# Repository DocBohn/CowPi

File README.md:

# CowPi Library

[//]: # ([![Depends on CowPi_stdio]&#40;https://img.shields.io/badge/🐮_𝜋_depends_on-CowPi__stdio-crimson&#41;]&#40;https://github.com/DocBohn/CowPi_stdio&#41;)
[//]: # (scarlet)
[)](https://github.com/DocBohn/CowPi_stdio)

## What is the Cow Pi?

### The hardware

The Cow Pi is a simple circuit that consists of a microcontroller board, a
display module, a couple of LEDs, a couple of momentary buttons, a couple of
maintained switches, and a matrix keypad. We use it to teach memory-mapped I/O,
polling, and interrupts.

### The library

Initially we supported the memory-mapped I/O lab with a header file that
defined some `struct`s and named constants. Later we added some macros to reduce
complexity that didn't contribute to the learning objectives.

We decided to create a library for three reasons:
- It allows us to provide some additional bootstrapping for students: they'll
  be able to work on polling logic using some of the functions in the library
  and then later replace those with functions that use memory-mapped I/O. Or
  they can start with memory-mapped I/O and then move on to the polling logic.
  Before the library, students had no choice but to start with memory-mapped
  I/O.
- It allows us to replace parameterized macros with functions.
- We can use more complex display modules. Originally, the Cow Pi's display
  module was an 8-digit/7-segment display module. The Terasic Altera DE1 boards
  that we used to use had a 4-digit/7-segment display. Manipulating 7-segment
  displays is incredibly easy. To simplify the supply chain for our supplier,
  we're going to try using 2-row/16-column LCD display modules. Manipulating
  the LCD1602 display modules is not incredibly easy. With a library, we can let
  students focus on the memory-mapped I/O aspect and not on the details of
  controlling the display module.

## Why is it called the *Cow Pi*?

Because it's punny.

### No, I mean, *-Pi* is typically used as a suffix for circuits that use a Raspberry Pi instead of an Arduino.

Typically, yes, but *Cowduino* isn't very punny, is it?

Besides, there soon will be a version of the Cow Pi that makes use of the
Raspberry Pi Pico. That's why we said that the circuit has "a microcontroller
board" instead of "an Arduino Nano."

## Why did you design something new? Didn't you consider something manufactured?

We used to use the [Terasic Altera
DE1](https://www.terasic.com.tw/cgi-bin/page/archive.pl?No=83). Our computer
science students and software engineering students didn't reprogram the FPGA;
they simply used C and compiled their programs to run on the Nios II soft core
that came pre-programmed into the FPGA. When we decided it was time to stop
using the DE1s, our computer engineering students switched to the [Terasic
DE10-Lite](http://de10-lite.terasic.com/), but we decided that the cost was too
great for the features that our CS and SE students would use.

The problem we ran into with the various Arduino shields or Raspberry Pi hats is
that they either were unavailable in the quantity we needed, or would require
our students to solder them together -- and we have no expectations that our
CS and SE students are able to solder. We were pretty sure that they could put
together a circuit on a solderless breadboard, though.

We are, however, planning to have PCBs manufactured and assembled, assuming we
can keep the cost down.

## The Cow Pi uses nearly all of the pins on the Arduino Nano; that'll make it hard to do any other projects with it.

Yes, that's true. The Cow Pi is designed to support specific learning
objectives. If you want to do a different project, then disassemble the kit and
use the parts to build your project.

## Why don't you just use existing libraries like `LiquidCrystal` and `Wire`?

Because those libraries hide the details. Part of what we use the Cow Pi for is
teaching memory-mapped I/O.

## Have you considered making the CowPi library work with MicroPython or CircuitPython?

😐

Python isn't exactly known for being a language that exposes the underlying
hardware. While it's possible to make the library work with MicroPython and/or
CircuitPython, that'd defeat the point of the library being a way to hide
*only* the complexities that are unrelated to memory-mapped I/O,
polling, and interrupts.

## Are you going to make it work with the XYZ microcontroller board?

Probably.

The Cow Pi works with the Arduino Nano and the Arduino Uno.

We have plans to make it work with the Arduino Mega 2560, the Arduino Nano
Every, the Arduino Nano 33 IOT, and the Raspberry Pi Pico (both using the
Arduino framework and using the Pico SDK). Probably the Raspberry Pi 4 and 400,
too. Eventually the Arduino Nano 33 BLE Sense, the Arduino RP2040 Connect, and
the Arduino Uno WiFi & Arduino Uno R4 (but we don't have samples of any of these laying
around).

### What about the STM32 "Blue Pill," or something in the Adafruit Feather family, or the SparkFun Teensy family, or...?

If there's interest using one of these microcontroller boards for the Cow Pi,
we can certainly look into it.

Similarly, if there's interest in a different display module, we can look into
it.

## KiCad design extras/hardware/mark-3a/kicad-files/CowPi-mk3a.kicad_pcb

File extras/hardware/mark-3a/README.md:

# Cow Pi Mark 3a PCB Assembly Notes

- I2C or SPI
  - There is a pair of solder jumpers on the left side of the board. Creating a
    solder bridge from each center pad to its top pad will connect the
    slide-switches to Arduino pins `D10` and `D11`, freeing the pins used for
    I2C. Creating a bridge from each center pad to its bottom pad will connect
    the slide-switches to pins `D18/A4` and `D19/A5`, freeing the pins used
    for SPI.
  - For I2C, the display module will be driven by a [common I2C interface board
    for LCD character displays](https://www.google.com/search?q=i2c+adapter+for+lcd+1602).
    Before soldering the interface module to the PCB, solder short wires to the
    `GND`, `5V`, `SDA`, and `SCL` solder pads near the located between the
    Arduino's footprint and the mini-breadboard's footprint. After soldering the
    interface module to the PCB, solder the other ends of those wires to the
    interface module's I2C headers.
  - For SPI, you'll need a 10kΩ trim potentiometer (the files in the repo are
    set up for 3 inline pins since that's what's in my junk drawer; you'll
    need to change the footprint if you want a different pin arrangement), a
    10kΩ fixed resistor, an NPN transistor (I'm using 2N2222), and a 74HC595
    shift register. If you want to have the option to disable the display
    module, then you'll also need a 3-pin male header and a shunt jumper;
    otherwise, you can create a solder bridge from the center `SPI-LCD1602
    Disable/Enable` hole to the `Enable` hole.
- Common [2-row, 16-column LCD character display](https://www.google.com/search?q=lcd+1602+display+module)
  ("LCD1602") driven by Hitachi HD44780 LCD controller.
- Slide-switches: two (2) common 3-pin, 2.54mm (0.1in) pitch, breadboard-mountable
  switches
- Tactile switches (buttons): nineteen (19) 6mm, 4-prong tactile switches
  (you could use only 18 if you omit the `RESET` button and just use the one
  on the Arduino)
- Diodes: sixteen (16) diodes; I originally planned to use 1N4001 but got a good
  deal on 1N4448. These are to permit safe and accurate reading of multiple
  keypad buttons simultaneously (not yet supported in the library a/o v0.3.0).
  If you'll only ever press one keypad button at a time, then you can create
  solder bridges across the diode holes instead of inserting diodes.
- LEDs: two (2) common LEDs. I like to use red for left and green for right, to
  match navigation lights, but that's not necessary. You can omit the left LED
  since it duplicate's the Arduino's build-in LED. For that matter, the left
  LED is nigh-useless when using SPI.
- Current-limiting resistors: two (2) common resistors. I spec'd 470Ω, but
  the value isn't critical as long as your choice sufficiently limits the current
  into the LEDs and leaves the LED bright enough to see.
- External power jack (optional): 2.1mm barrel connector
- 4-input NAND -- because of the limited number of external interrupts on the
  ATmega328P (and, by exension, the Arduino Nano), we use NANDs to generate
  the interrupt signals for the keypad and for the left/right buttons. (Early
  testing confirms that the NANDs won't be needed when using an Arduino Nano
  Every due to the ample external interrupts, but the CowPi library doesn't yet
  support that (a/o v0.3.0).) We originally used 74LS20, but *any* 74x20 should
  do (we're currently using 74HC20 because they're a little cheaper and also
  have a broader Vcc range). If you want to selectively break the connection
  from the 74x20 to the Arduino, then add two (2) 2-pin male headers to the
  appropriate location near the Arduino and close the circuit with shunt jumpers;
  if you think you'll never break that circuit, then you can create solder
  bridges where the male headers would otherwise go.
- Breakout header (optional): 2x8-pin, 2.54 (0.1in) pitch, female header. It
  doesn't break out all of the Arduino pins, only those that might be available
  for use by external components
- Mini-breadboard (optional): a convenient place to mount external components,
  also a convenient way to hide the order number printed on the PCB. Note that
  the mini-breadboard I used to measure the space needed didn't have interlocking
  tabs, and the mini-breadboards I ordered to place on the PCBs do -- those tabs
  make for a tight squeeze, so place the mini-breadboard on last.

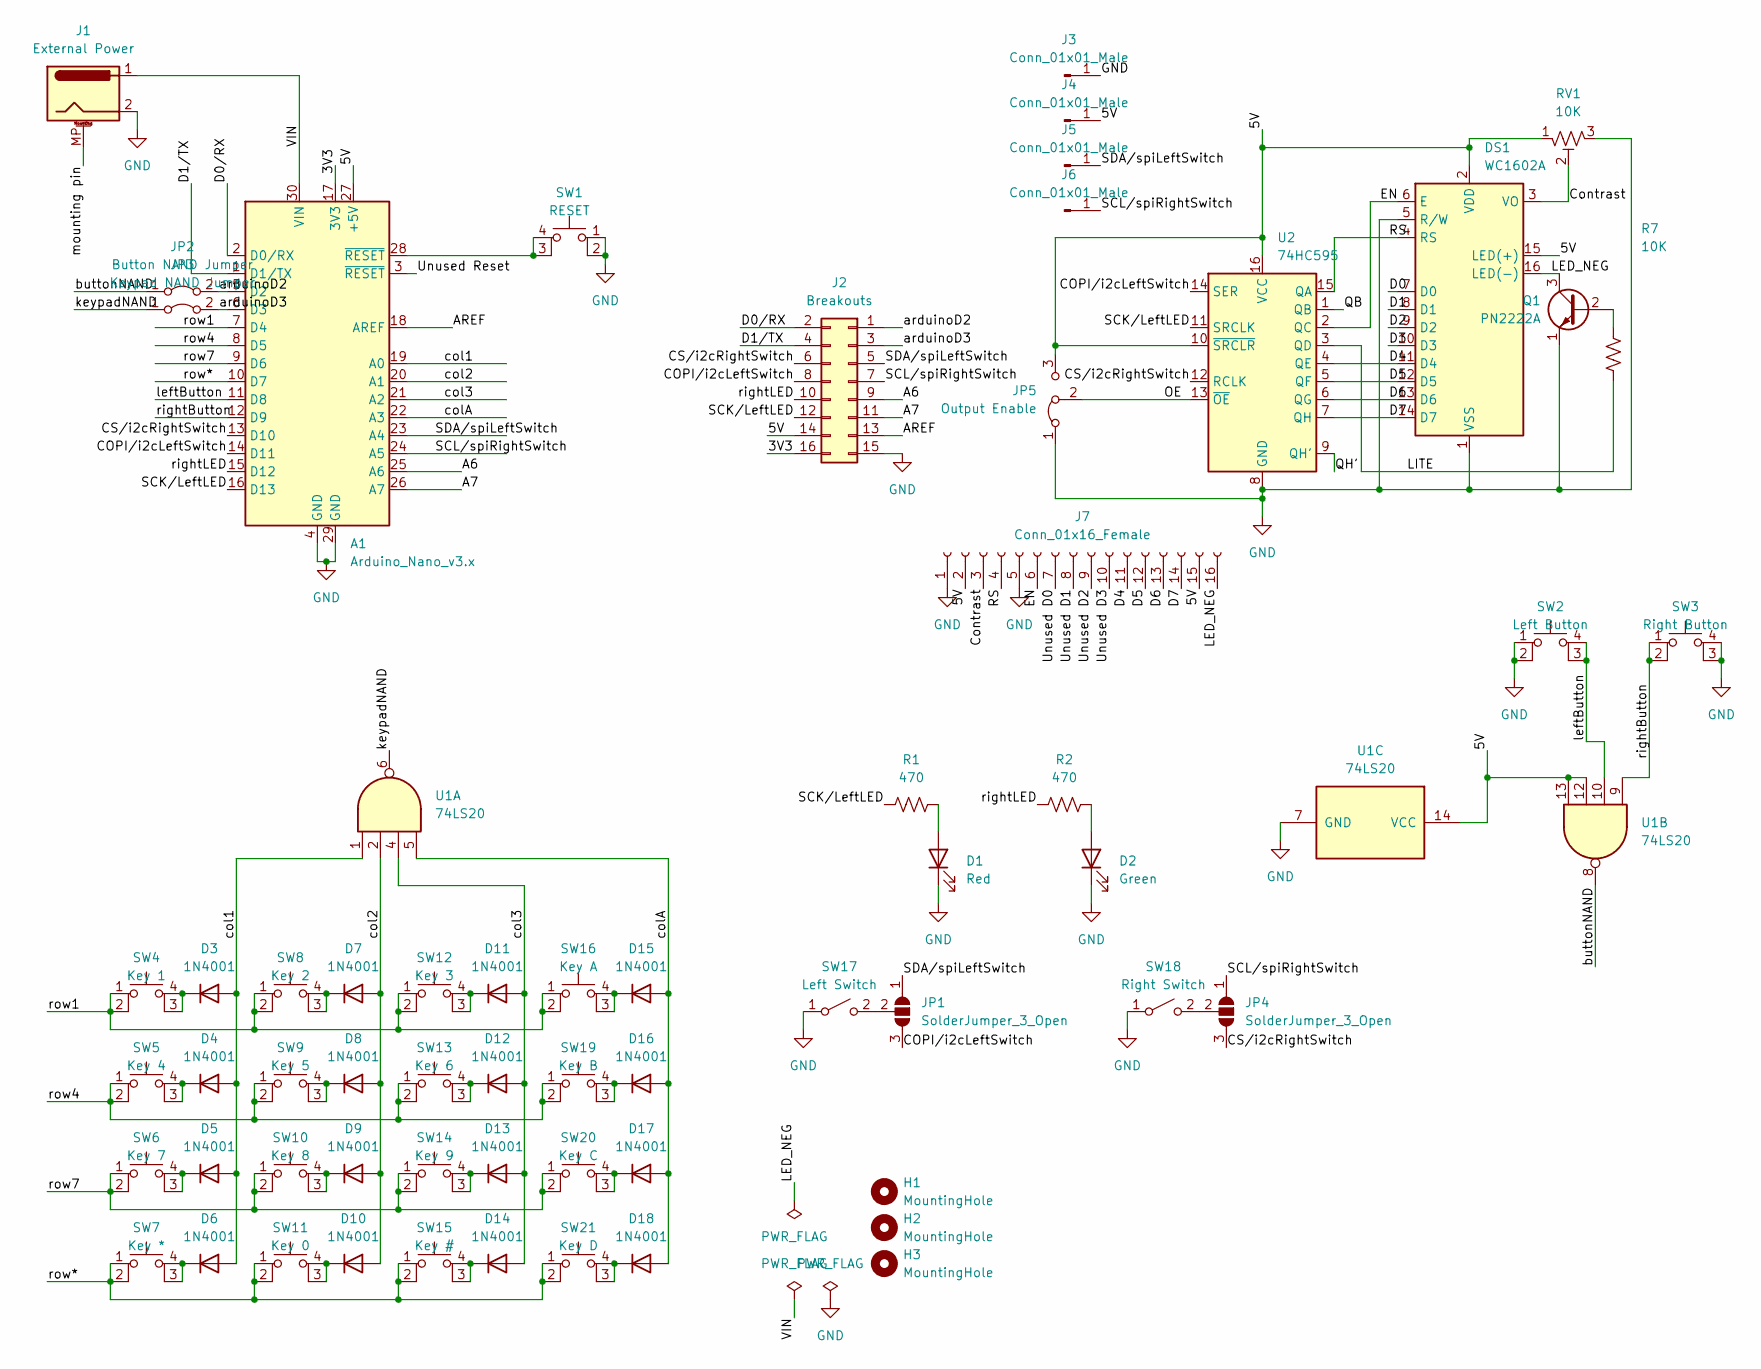
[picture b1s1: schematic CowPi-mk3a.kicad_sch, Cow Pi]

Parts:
A1: Arduino_Nano_v3.x; Arduino_Nano
D1: Red; LED_D5.0mm
D2: Green; LED_D5.0mm
D3, D4, D5, D6, D7, D8, D9, D10, D11, D12, D13, D14, D15, D16, D17, D18: 1N4001; D_DO-41_SOD81_P10.16mm_Horizontal
DS1: WC1602A
H1, H2, H3: MountingHole; MountingHole_3mm_Pad
J1: External Power; BarrelJack_Horizontal
J2: Breakouts; PinSocket_2x08_P2.54mm_Vertical
J3, J4, J5, J6: Conn_01x01_Male; TestPoint_Pad_D2.0mm
J7: Conn_01x16_Female; PinSocket_1x16_P2.54mm_Vertical
JP1, JP4: SolderJumper_3_Open; SolderJumper-3_P1.3mm_Open_RoundedPad1.0x1.5mm
JP2: Button NAND Jumper; PinHeader_1x02_P2.54mm_Vertical
JP3: Keypad NAND Jumper; PinHeader_1x02_P2.54mm_Vertical
JP5: Output Enable; PinHeader_1x03_P2.54mm_Vertical
Q1: PN2222A; TO-92_Inline
R1, R2: 470; R_Axial_DIN0309_L9.0mm_D3.2mm_P12.70mm_Horizontal
R7: 10K; R_Axial_DIN0309_L9.0mm_D3.2mm_P12.70mm_Horizontal
RV1: 10K; Potentiometer_Vishay_248GJ-249GJ_Single_Vertical
SW1: RESET; SW_PUSH_6mm_H5mm
SW2: Left Button; SW_PUSH_6mm_H5mm
SW3: Right Button; SW_PUSH_6mm_H5mm
SW4: Key 1; SW_PUSH_6mm_H5mm
SW5: Key 4; SW_PUSH_6mm_H5mm
SW6: Key 7; SW_PUSH_6mm_H5mm
SW7: Key *; SW_PUSH_6mm_H5mm
SW8: Key 2; SW_PUSH_6mm_H5mm
SW9: Key 5; SW_PUSH_6mm_H5mm
SW10: Key 8; SW_PUSH_6mm_H5mm
SW11: Key 0; SW_PUSH_6mm_H5mm
SW12: Key 3; SW_PUSH_6mm_H5mm
SW13: Key 6; SW_PUSH_6mm_H5mm
SW14: Key 9; SW_PUSH_6mm_H5mm
SW15: Key #; SW_PUSH_6mm_H5mm
SW16: Key A; SW_PUSH_6mm_H5mm
SW17: Left Switch; SW_Slide_1P2T_CK_OS102011MS2Q
SW18: Right Switch; SW_Slide_1P2T_CK_OS102011MS2Q
SW19: Key B; SW_PUSH_6mm_H5mm
SW20: Key C; SW_PUSH_6mm_H5mm
SW21: Key D; SW_PUSH_6mm_H5mm
U1: 74LS20; DIP-14_W7.62mm_Socket
U2: 74HC595; DIP-16_W7.62mm_Socket

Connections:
/3V3: A1.17 (3V3), J2.16
/5V: A1.27 (+5V), DS1.2 (VDD), DS1.15 (LED(+)), J2.14, J4.1, J7.2, J7.15, JP5.3 (B), RV1.1, U1.12, U1.13, U1.14 (VCC), U2.10 (~SRCLR), U2.16 (VCC)
/A6: A1.25 (A6), J2.9
/A7: A1.26 (A7), J2.11
/AREF: A1.18 (AREF), J2.13
/COPI/i2cLeftSwitch: A1.14 (D11), J2.8, JP1.3 (B), U2.14 (SER)
/CS/i2cRightSwitch: A1.13 (D10), J2.6, JP4.3 (B), U2.12 (RCLK)
/Contrast: DS1.3 (VO), J7.3, RV1.2
/D0: DS1.7 (D0)
/D0/RX: A1.2 (D0/RX), J2.2
/D1: DS1.8 (D1)
/D1/TX: A1.1 (D1/TX), J2.4
/D2: DS1.9 (D2)
/D3: DS1.10 (D3)
/D4: DS1.11 (D4), J7.11, U2.4 (QE)
/D5: DS1.12 (D5), J7.12, U2.5 (QF)
/D6: DS1.13 (D6), J7.13, U2.6 (QG)
/D7: DS1.14 (D7), J7.14, U2.7 (QH)
/EN: DS1.6 (E), J7.6, U2.2 (QC)
/LED_NEG: DS1.16 (LED(-)), J7.16, Q1.3 (C)
/LITE: R7.2, U2.3 (QD)
/OE: JP5.2 (C), U2.13 (~OE)
/QB: U2.1 (QB)
/QH': U2.9 (QH')
/RS: DS1.4 (RS), J7.4, U2.15 (QA)
/SCK/LeftLED: A1.16 (D13), J2.12, R1.1, U2.11 (SRCLK)
/SCL/spiRightSwitch: A1.24 (A5), J2.7, J6.1, JP4.1 (A)
/SDA/spiLeftSwitch: A1.23 (A4), J2.5, J5.1, JP1.1 (A)
/Unused D0: J7.7
/Unused D1: J7.8
/Unused D2: J7.9
/Unused D3: J7.10
/Unused Reset: A1.3 (~RESET)
/VIN: A1.30 (VIN), J1.1
/arduinoD2: A1.5 (D2), J2.1, JP2.2 (B)
/arduinoD3: A1.6 (D3), J2.3, JP3.2 (B)
/buttonNAND: JP2.1 (A), U1.8
/col1: A1.19 (A0), D3.2 (A), D4.2 (A), D5.2 (A), D6.2 (A), U1.1
/col2: A1.20 (A1), D7.2 (A), D8.2 (A), D9.2 (A), D10.2 (A), U1.2
/col3: A1.21 (A2), D11.2 (A), D12.2 (A), D13.2 (A), D14.2 (A), U1.4
/colA: A1.22 (A3), D15.2 (A), D16.2 (A), D17.2 (A), D18.2 (A), U1.5
/keypadNAND: JP3.1 (A), U1.6
/leftButton: A1.11 (D8), SW2.3 (K), SW2.4 (A), U1.10
/mounting pin: J1.MP (MountPin)
/rightButton: A1.12 (D9), SW3.1, SW3.2, U1.9
/rightLED: A1.15 (D12), J2.10, R2.1
/row1: A1.7 (D4), SW4.1, SW4.2, SW8.1, SW8.2, SW12.1, SW12.2, SW16.1, SW16.2
/row4: A1.8 (D5), SW5.1, SW5.2, SW9.1, SW9.2, SW13.1, SW13.2, SW19.1, SW19.2
/row7: A1.9 (D6), SW6.1, SW6.2, SW10.1, SW10.2, SW14.1, SW14.2, SW20.1, SW20.2
/row*: A1.10 (D7), SW7.1, SW7.2, SW11.1, SW11.2, SW15.1, SW15.2, SW21.1, SW21.2
GND: A1.4 (GND), A1.29 (GND), D1.1 (K), D2.1 (K), DS1.1 (VSS), DS1.5 (R/W), J1.2, J2.15, J3.1, J7.1, J7.5, JP5.1 (A), Q1.1 (E), RV1.3, SW1.1, SW1.2, SW2.1, SW2.2, SW3.3 (K), SW3.4 (A), SW17.1 (A), SW18.1 (A), U1.7 (GND), U2.8 (GND)
unnamed: A1.28 (~RESET), SW1.3 (K), SW1.4 (A)
unnamed: D1.2 (A), R1.2
unnamed: D2.2 (A), R2.2
unnamed: D3.1 (K), SW4.3 (K), SW4.4 (A)
unnamed: D4.1 (K), SW5.3 (K), SW5.4 (A)
unnamed: D5.1 (K), SW6.3 (K), SW6.4 (A)
unnamed: D6.1 (K), SW7.3 (K), SW7.4 (A)
unnamed: D7.1 (K), SW8.3 (K), SW8.4 (A)
unnamed: D8.1 (K), SW9.3 (K), SW9.4 (A)
unnamed: D9.1 (K), SW10.3 (K), SW10.4 (A)
unnamed: D10.1 (K), SW11.3 (K), SW11.4 (A)
unnamed: D11.1 (K), SW12.3 (K), SW12.4 (A)
unnamed: D12.1 (K), SW13.3 (K), SW13.4 (A)
unnamed: D13.1 (K), SW14.3 (K), SW14.4 (A)
unnamed: D14.1 (K), SW15.3 (K), SW15.4 (A)
unnamed: D15.1 (K), SW16.3 (K), SW16.4 (A)
unnamed: D16.1 (K), SW19.3 (K), SW19.4 (A)
unnamed: D17.1 (K), SW20.3 (K), SW20.4 (A)
unnamed: D18.1 (K), SW21.3 (K), SW21.4 (A)
unnamed: JP1.2 (C), SW17.2 (B)
unnamed: JP4.2 (C), SW18.2 (B)
unnamed: Q1.2 (B), R7.1

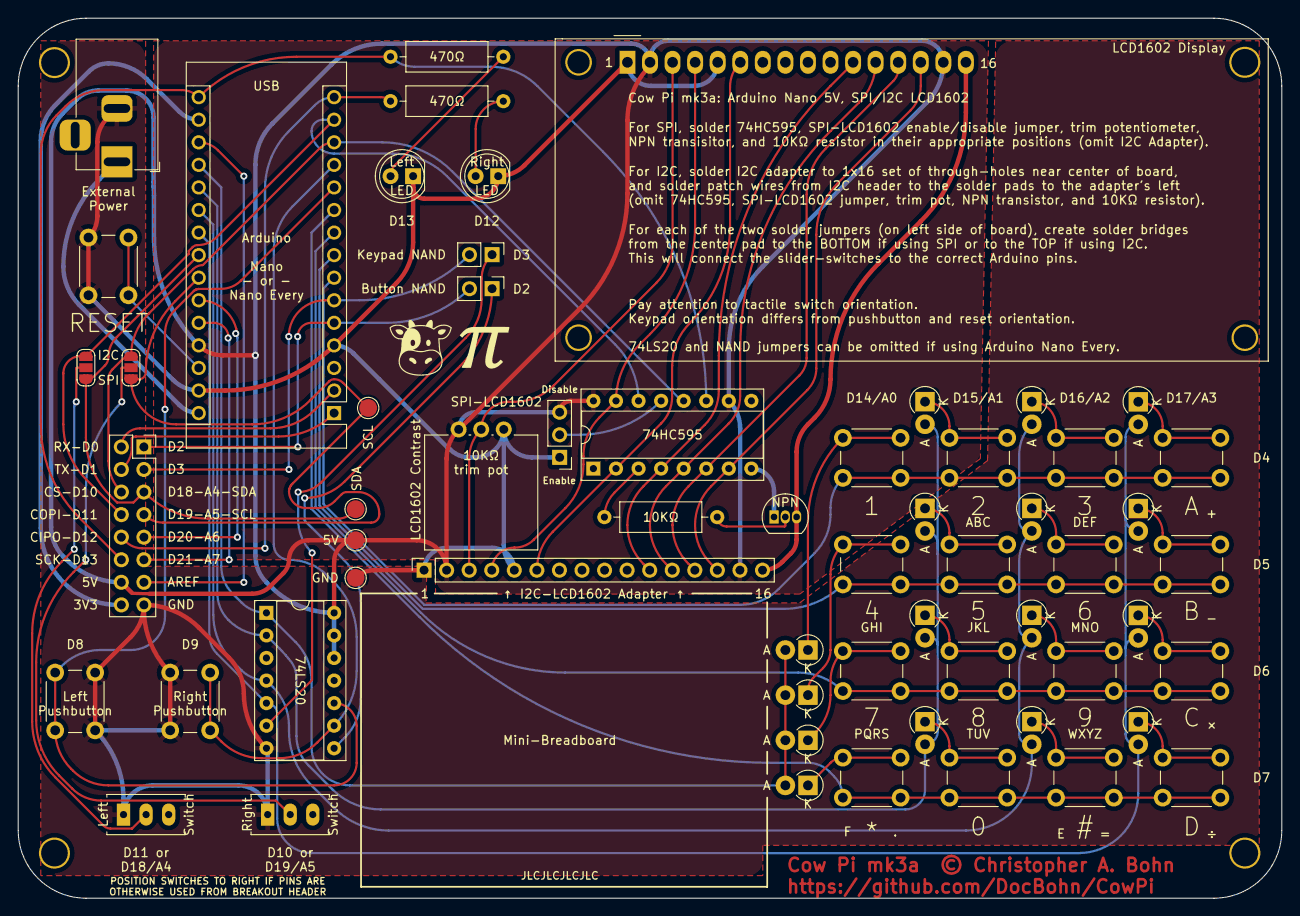
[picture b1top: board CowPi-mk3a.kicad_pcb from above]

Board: 2 copper layers, 142.2 x 99.1 mm, 63 parts (0 on the bottom side), 61 nets.

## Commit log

2022-08-17 Migrated CowPi library to its own repository
2022-08-18 Added Cow Pi hardware Mark 1 instructions and Mark 3a PCB files
2022-10-06 Making progress on datasheet
2022-11-08 datasheet ready for PollingLab
2022-11-16 added ATmega328P-specific data to datasheet
2022-11-16 removed doxygen files from datasheet directory
2023-01-26 Resolved problem with symbols being introduced too often. Fixes #3
    - Migrated font constants to "internal" headers that are imported *only*
    by cowpi_fonts.c.
    - Replaced `cowpi_io_base` constant pointer with `COWPI_IO_BASE` macro
2023-01-26 Removed error detection from default I2C code. Fixes #2
    Besides requiring the "one additional handshake" the error detection
    code suggested in the ATmega328P datasheet was also causing problems
    when included in student code. Experimentation in a simulator indicated
    that a "data received ACK" was present after a START bit was sent. My
    working hypothesis is that the problem happens when the system is reset
    while the I2C peripheral is expecting data, causing a misinterpretation
2023-01-26 Created COWPI_DEFAULT mapping for SPI control of LCD1602. Closes #1
2023-01-26 Added the verb "is" to functions that detect switches' position.
2023-01-26 Documentation updates for change to version 0.4
2023-03-19 Changes in preparation for Spring 2023 PollingLab
    The biggest change is a new table that shows which devices are read
    from or written to by which bits in the I/O registers.
2023-04-05 updated diagrams
2023-04-06 Removed bug that constrained the include order for nested headers
    When the Arduino IDE autommatically included a nested header file
    upon auto-complete, it caused some headers (such as cowpi_io.h)
    that depended on stdbool.h to be included before stdbool.h was
    included.
    The fix is to make sure that the nested headers include any
    standard headers they actually depend on, instead of relying on
2023-04-29 Inserted use of "dummy_pgmspace" into appropriate files
2023-05-09 Added file streams for top and bottom rows of LCD1602 display
    Allows use of `fprintf` to send strings to the display module
2023-05-16 Added file stream for full LCD1602 display
    Where the row-based file streams allow the programmer to determine text
    placement by using one stream or another, the full-display file stream
    requires the programmer to use ASCII placement codes -- but it's
    possible that the `\n` behavior is more intuitive by doing so.
    It's probable that only one approach or the other will still be around
    when we get to the 1.0 release.
2023-05-17 Added functions to register/deregister ISR for changes on any Nano pin
    Strictly speaking, there are still just the three ISRs, one for each
    "real" pin change interrupt. The actual ISRs then check which pin had
    the change and call the appropriate interrupt handler that the
    programmer registered.
2023-05-20 Replaced Wokwi diagram files (closes #12)
    While Wokwi now has logic gates, the ability to register ISRs for
    changes on specific pins other than D2 & D3 (see commit b362454), logic
    gates are no longer necessary.
    We now have a template diagram, as well as diagrams with specific
    display modules.
2023-07-06 Updated library manifests
2023-07-06 Removed Display-Related Code
    All code related to display modules and to stdin/stdout is now in the
    CowPi_stdio library.
2023-07-07 Default kepad implementation can handle different microcontroller boards
2023-07-07 Added function to read chorded keypresses
    This function should only be called when diodes protect the keys!
2023-07-24 Updated `cowpi_setup` to use `CowPi_stdio` configuration structures
    Also some internal file re-arranging.
2023-07-31 Removed Doxygen groups to better support Breathe and ReadTheDocs
2023-08-02 Push to v0.6
2023-08-13 Added pin mappings for Raspberry Pi Pico
    Still no memory mapped I/O structures.
    Still only for Arduino framework.
2023-10-14 Added Nyquist Rate check to debouncing code
2023-11-25 Added structs for access to RP2040 memory-mapped I/O registers
    Pin registers are tested; other structures are implemented but need
    to be tested.
    Addresses #20
2024-03-03 Push to 0.7
2024-03-08 More compliant with C standard
    Some compilers enforce requirement that static variables be initialized
    with constants, as opposed to being initialized with const variables.
2024-08-07 Updated names of constants from CowPi_stdio
2024-08-08 Port to earlephilower/arduino-pico platform
2024-08-13 Added functions to configure input/output pins
    Primarily, this is to capture pin settings to facilitate pin interrupt
    configuration when using Arduino core backed by MBED.
    As a secondary benefit, this will eventually help reduce "shotgun
    surgery" when porting the library to non-Arduino frameworks.
2024-10-24 Interrupt updates
    - pin interrupt registration for MBED
    - timer interrupt configuration & registration for AVR & MBED
2024-10-27 Bugfix: replaced pinMode with cowpi_pin_mode from CowPi_stdio
2024-10-27 Corrected library manifests

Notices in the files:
extras/hardware/mark-3a/kicad-files/CowPi-mk3a.kicad_pcb:
Cow Pi mk3a  © Christopher A. Bohn
